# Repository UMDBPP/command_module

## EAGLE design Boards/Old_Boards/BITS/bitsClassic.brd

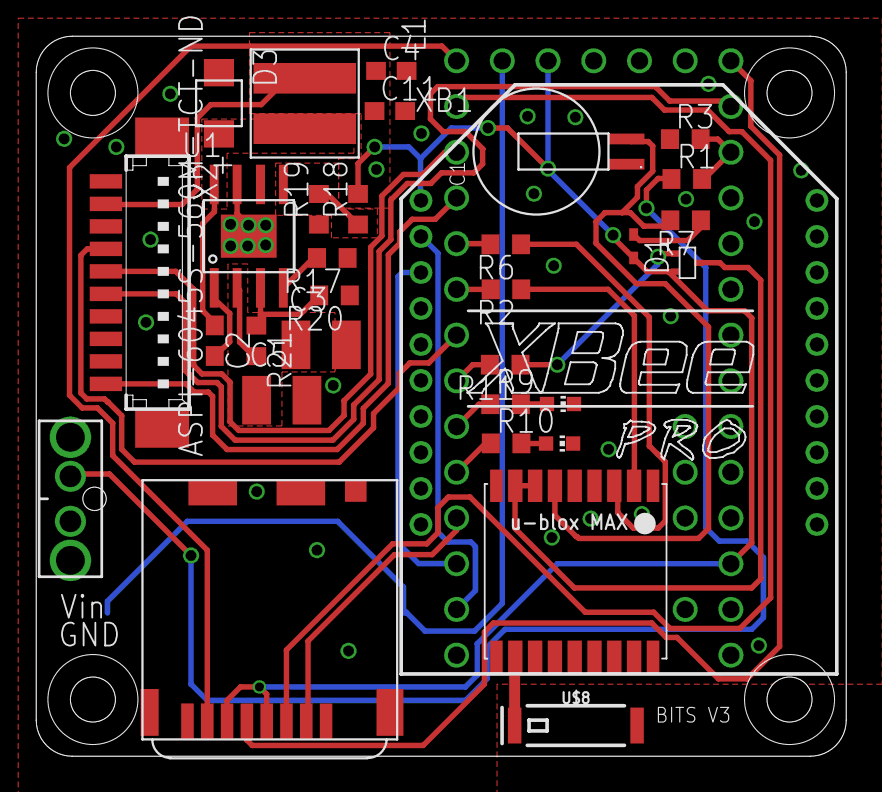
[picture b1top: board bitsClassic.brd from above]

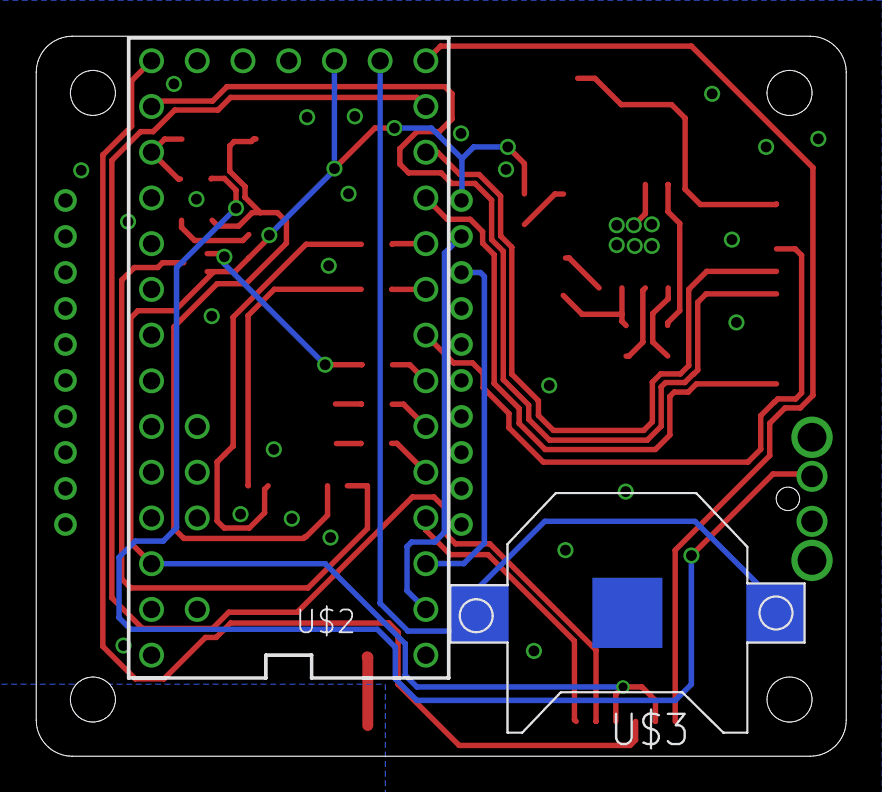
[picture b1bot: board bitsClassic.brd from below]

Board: 2 copper layers, 45.0 x 40.0 mm, 34 parts (2 on the bottom side), 34 nets.

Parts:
C1: ELNASUPERCAP
C2: .1 uF; C0603
C3: 10 uF; C1210
C4: .18 uF; C0603
C5: 2.2 uF; C1210
C11: 10 uF; C0603
D1: SOD523
D3: DO-214AC
L1: ASPI-6045S-560M-TCT-ND; ABRACON
LED1: Red; CHIP-LED0603
LED2: Green; CHIP-LED0603
R1: 18k; R0603
R2, R6, R7: 22; R0603
R3: 10k; R0603
R9, R10: 470; R0603
R11: 100; R0603
R17: 23.3k; R0603
R18: 45k; R0603
R19: 13.3k; R0603
R20: 31.6k; R0603
R21: 190k; R0603
T1: SI1013; SC-75
U1: LMR16020; SO8
U$1: MOLEX_NANOFIT_2
U$2: TEENSY_3.1-3.2_ALL_PINS; TEENSY_3.0-3.2&LC_ALL_PINS
U$3: CR1220SMT; CR1220-SMD
U$4: MICRO_SD; MICRO_SD_HINGED
U$7: MAX-M8
U$8: 1.575GHz; SPARKFUN-GPS_ANT-GPS-2X7MM
X2: 53398-10
XB1: XBEE-PRO

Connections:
+3V3: C4.1, C11.1, D1.A, L1.P$2, R18.2, T1.P$2, U$2.3.3V, U$2.3.3V1, U$4.VDD, U$4.VSS, X2.9, XB1.1
BAT_CELL1: R1.2, R3.2, U$2.15/A1
DIN: U$2.1, XB1.3
DOUT: U$2.0, XB1.2
FB: R18.1, R19.2, U1.P$5
GND: C1.GND, C3.2, C4.2, C5.2, C11.2, D3.P$1, LED1.C, LED2.C, R3.1, R17.1, R19.1, R20.1, U1.P$7, U1.PAD, U$1.P$2, U$2.GND, U$2.GND1, U$3.-, U$4.CD1, U$4.GND1, U$4.GND2, U$4.GND3, U$4.GND4, U$7.1_GND, U$7.10_GND, U$7.12_GND, X2.10, XB1.10
GPSON: R11.2, U$2.5
IN1: C3.1, C5.1, R1.1, R21.2, U1.P$2, U$1.P$1
LED1: R9.1, U$2.4
LED2: R10.1, U$2.3
MISO: U$2.12, U$4.DAT0
MOSI: U$2.11, U$4.CMD
unnamed: U$7.11_RF_IN, U$8.1
unnamed: D1.C, R7.1
unnamed: R6.1, U$7.3_RXD
unnamed: R2.1, U$7.2_TXD
unnamed: LED2.A, R10.2
unnamed: LED1.A, R9.2
unnamed: R11.1, T1.P$1
unnamed: T1.P$3, U$7.7_VCC_IO, U$7.8_VCC
unnamed: R17.2, U1.P$4
unnamed: C2.2, U1.P$1
unnamed: R20.2, R21.1, U1.P$3
RING: U$2.14/A0, X2.5
RX3: R2.2, U$2.7
RXD: U$2.9, X2.1
SCK: U$2.13, U$4.CLK
SD_CS: U$2.2, U$4.CD
SLEEP: U$2.6, X2.7
SW: C2.1, D3.P$2, L1.P$1, U1.P$8
TX3: R6.2, U$2.8
TXD: U$2.10, X2.6
VBAT: U$2.VBAT, U$3.+$1, U$3.+$2
V_BCKP: C1.3V3, R7.2, U$7.6_V_BCKP

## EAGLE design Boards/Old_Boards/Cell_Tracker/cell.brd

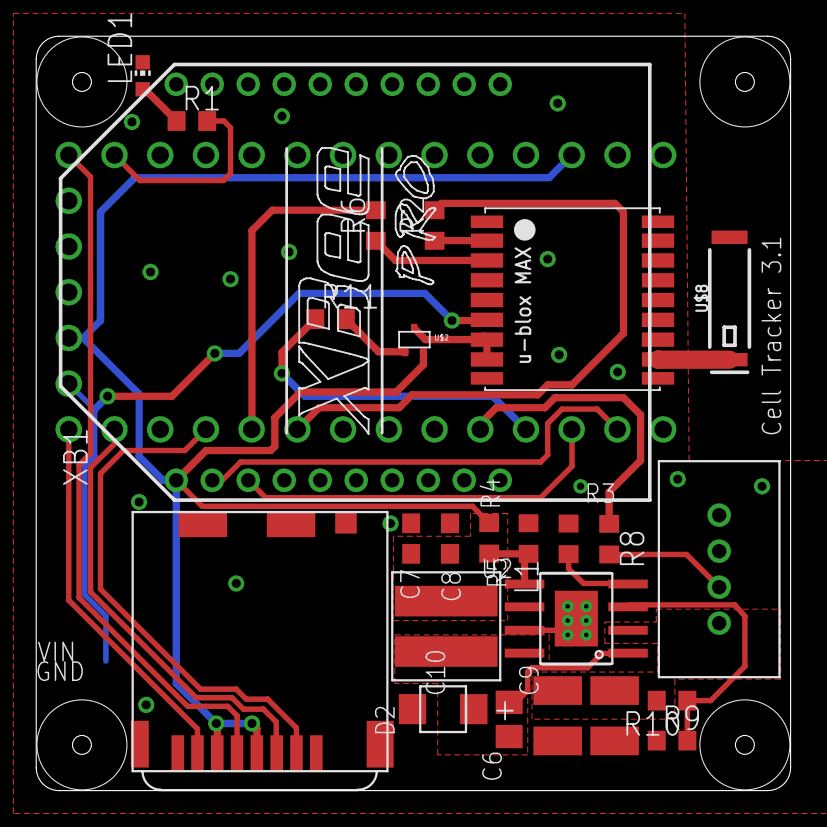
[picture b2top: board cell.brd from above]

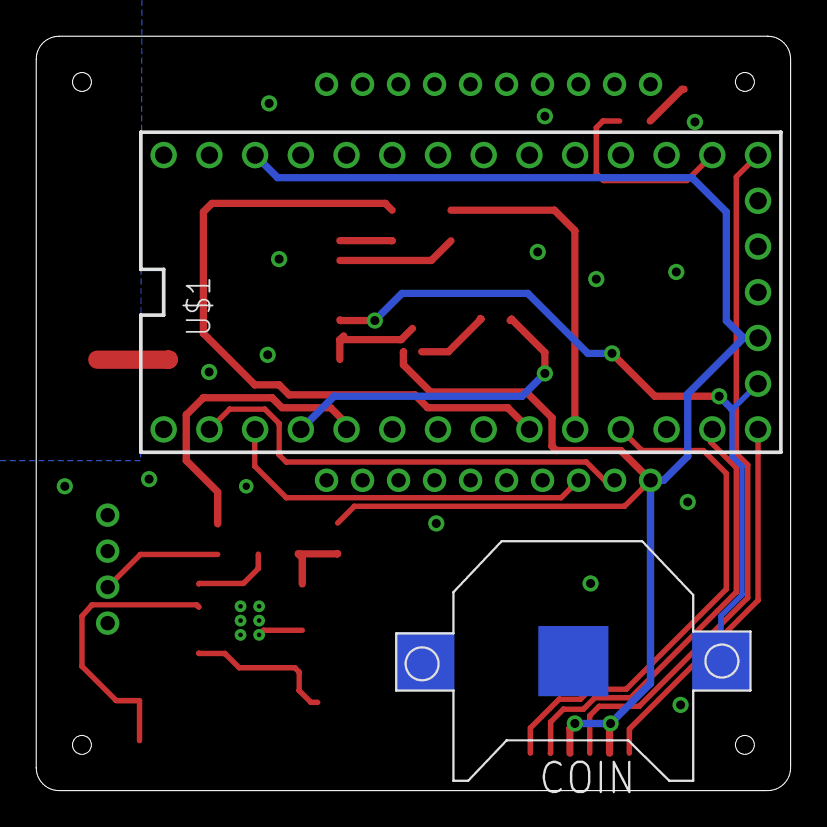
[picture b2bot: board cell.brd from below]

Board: 2 copper layers, 41.9 x 41.9 mm, 27 parts (2 on the bottom side), 27 nets.

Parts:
C6: 47 uF; C0805
C7: .18 uF; C0603
C8: 10 uF; C0603
C9: 10 uF; C1210
C10: 2.2 uF; C1210
COIN: CR1220SMD; CR1220-SMD
D2: DO-214AC
L1: ASPI-6045S-560M-TCT-ND; ABRACON
LED1: Green; CHIP-LED0603
R1: 470; R0603
R2, R6: 22; R0603
R3: 23.3k; R0603
R4: 45k; R0603
R5: 13.3k; R0603
R8: R0603
R9: 39k; R0603
R10: 195k; R0603
R11: 100; R0603
U2: LMR16020; SO8
U$1: TEENSY_3.1-3.2_OUTER_ROW; TEENSY_3.0-3.2&LC_OUTER_ROW
U$2: SI1013; SC-75
U$3: MICRO_SD; MICRO_SD_HINGED
U$4: MICROCLASP_4; 4_PIN_MICROCLASP
U$7: MAX-M8
U$8: 1.575GHz; SPARKFUN-GPS_ANT-GPS-2X7MM
XB1: XBEE-LTE-M; XBEE-PRO

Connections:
+3V3: C7.1, C8.1, L1.P$2, R4.2, U$1.3.3V, U$1.3.3V1, U$2.P$2, U$3.VDD, U$3.VSS, XB1.1
EN: R9.2, R10.1, U2.P$3
FB: R4.1, R5.2, U2.P$5
GND: C7.2, C8.2, C9.2, C10.2, COIN.-, D2.P$1, LED1.C, R3.1, R5.1, R9.1, U2.P$7, U2.PAD, U$1.GND, U$1.GND1, U$3.CD1, U$3.GND1, U$3.GND2, U$3.GND3, U$3.GND4, U$4.P$3, U$4.P$4, U$7.1_GND, U$7.10_GND, U$7.12_GND, XB1.10
GPSON: R11.1, U$1.2
MISO: U$1.12, U$3.DAT0
MOSI: U$1.11, U$3.CMD
unnamed: U$7.11_RF_IN, U$8.1
unnamed: R1.2, U$1.14/A0
unnamed: R6.1, U$7.3_RXD
unnamed: R2.1, U$7.2_TXD
unnamed: R11.2, U$2.P$1
unnamed: R3.2, U2.P$4
unnamed: C6.2, U2.P$1
unnamed: LED1.A, R1.1
unnamed: U$2.P$3, U$7.7_VCC_IO, U$7.8_VCC
unnamed: R8.2, U$4.P$1
RX1: U$1.0, XB1.2
RX3: R2.2, U$1.7
SCK: U$1.13, U$3.CLK
SD_CS: U$1.9, U$3.CD
SW: C6.1, D2.P$2, L1.P$1, U2.P$8
SWITCH_LED: R8.1, U$1.3
TX1: U$1.1, XB1.3
TX3: R6.2, U$1.8
VIN: C9.1, C10.1, R10.2, U2.P$2, U$4.P$2
V_BCKP: COIN.+$1, U$1.VBAT, U$7.6_V_BCKP

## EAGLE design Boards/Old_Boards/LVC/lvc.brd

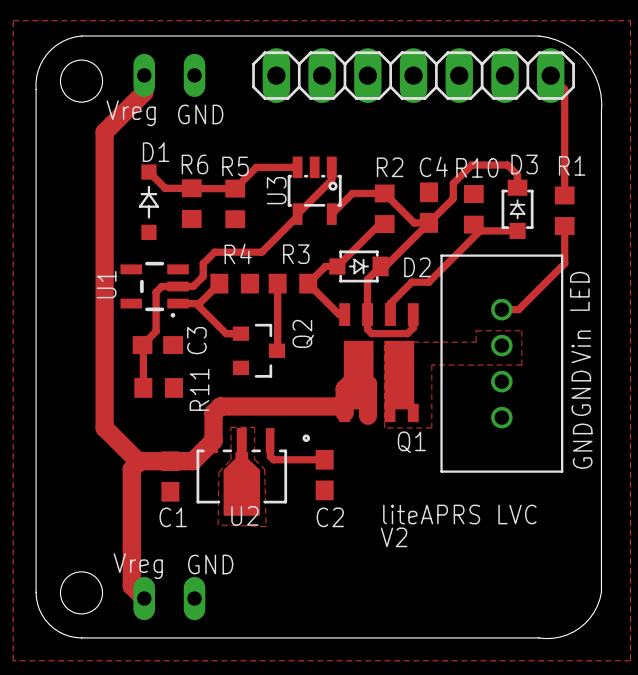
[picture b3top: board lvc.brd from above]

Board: 2 copper layers, 31.4 x 33.5 mm, 24 parts (0 on the bottom side), 13 nets.

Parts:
C1: 0.33uF; C0603
C2, C4: 0.1uF; C0603
C3: 47pF; C0603
D1: BZT52B8V2; SOD123
D2, D3: DZ2J120M0L; SMINI2-F5-B
JP2: 1X07
Q1: SI7997DP; POWERPAK-SO-8-DUAL
Q2: RK7002BMT116; SOT23
R1: R0603
R2, R4, R11: 100k; R0603
R3: 3k; R0603
R5, R6, R10: 1M; R0603
U1: NCP300LSN33T1G; SOT23-5
U2: L78L33ACUTR; SOT-89
U3: TLV170IDBVR; SOT23-DBV
U$1: MICROCLASP_4; 4_PIN_MICROCLASP
U$2, U$3: LITEAPRS

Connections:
GND: C1.2, C2.2, C3.2, C4.2, D1.A, Q2.2, R4.2, R6.2, R10.2, R11.1, U1.3, U2.2, U3.2, U$1.P$3, U$1.P$4, U$2.P$2, U$3.P$2
LED: C2.1, U2.1
LOAD: Q2.1, R4.1, U1.1
unnamed: R1.2, U$1.P$2
unnamed: D2.A, Q1.4, R2.2, R3.1
unnamed: D3.A, Q1.2, R10.1
unnamed: Q2.3, R3.2
STATUS: JP2.1, R1.1
V+: C4.1, D2.C, D3.C, Q1.1, Q1.3, R2.1, U3.5
VDD: Q1.7, Q1.8, Q1.8L, U$1.P$1
VREG: C1.1, Q1.5, Q1.5L, Q1.6, U2.3, U$2.P$1, U$3.P$1
V_DIV: D1.C, R5.2, R6.1, U3.3
V_DIV_BUF: C3.1, R11.2, U1.2, U3.1, U3.4

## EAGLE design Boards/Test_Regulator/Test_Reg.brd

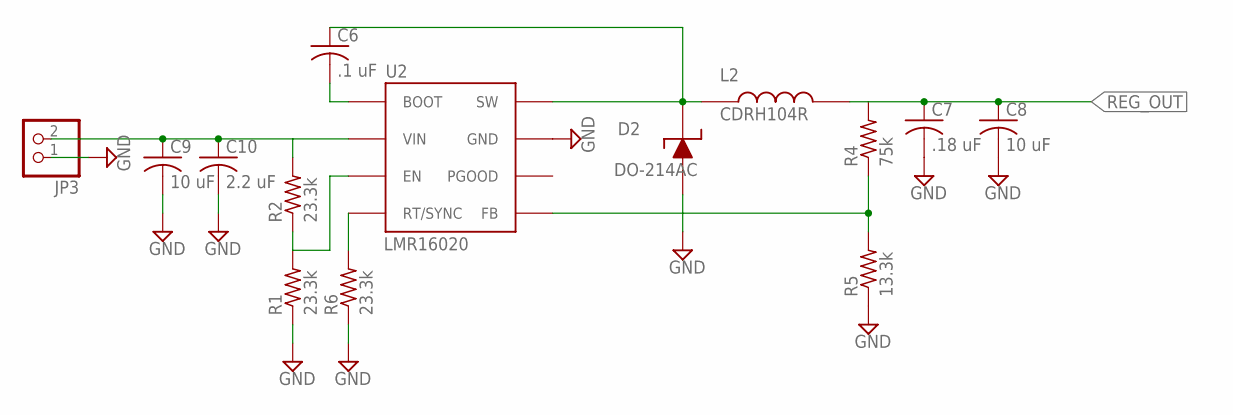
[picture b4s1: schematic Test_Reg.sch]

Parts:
C6: .1 uF; C0603
C7: .18 uF; C0603
C8: 10 uF; C0603
C9: 10 uF; C1210
C10: 2.2 uF; C1210
D2: DO-214AC
JP3: PINHD-1X2; 1X02
L2: CDRH104R
R1, R2, R6: 23.3k; R0603
R4: 75k; R0603
R5: 13.3k; R0603
U2: LMR16020; SO8

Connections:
GND: C7.2, C8.2, C9.2, C10.2, D2.P$1, JP3.1, R1.1, R5.1, R6.1, U2.P$7 (GND), U2.PAD (GND)
IN: C9.1, C10.1, JP3.2, R2.2, U2.P$2 (VIN)
unnamed: R6.2, U2.P$4 (RT/SYNC)
unnamed: R1.2, R2.1, U2.P$3 (EN)
unnamed: C6.2, U2.P$1 (BOOT)
unnamed: C6.1, D2.P$2, L2.P$1, U2.P$8 (SW)
unnamed: R4.1, R5.2, U2.P$5 (FB)
REG_OUT: C7.1, C8.1, L2.P$2, R4.2

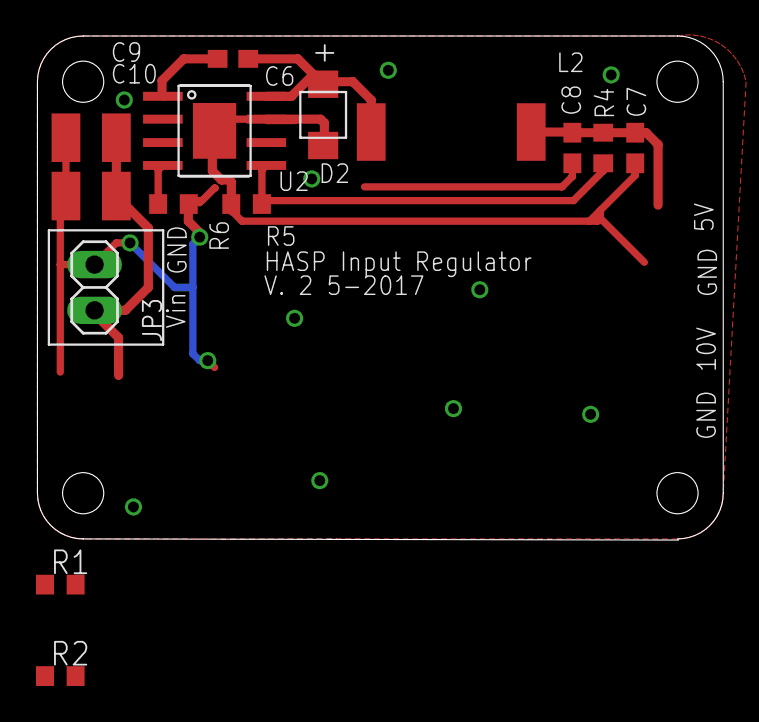
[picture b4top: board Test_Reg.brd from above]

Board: 2 copper layers, 38.1 x 28.0 mm, 14 parts (0 on the bottom side), 8 nets.
